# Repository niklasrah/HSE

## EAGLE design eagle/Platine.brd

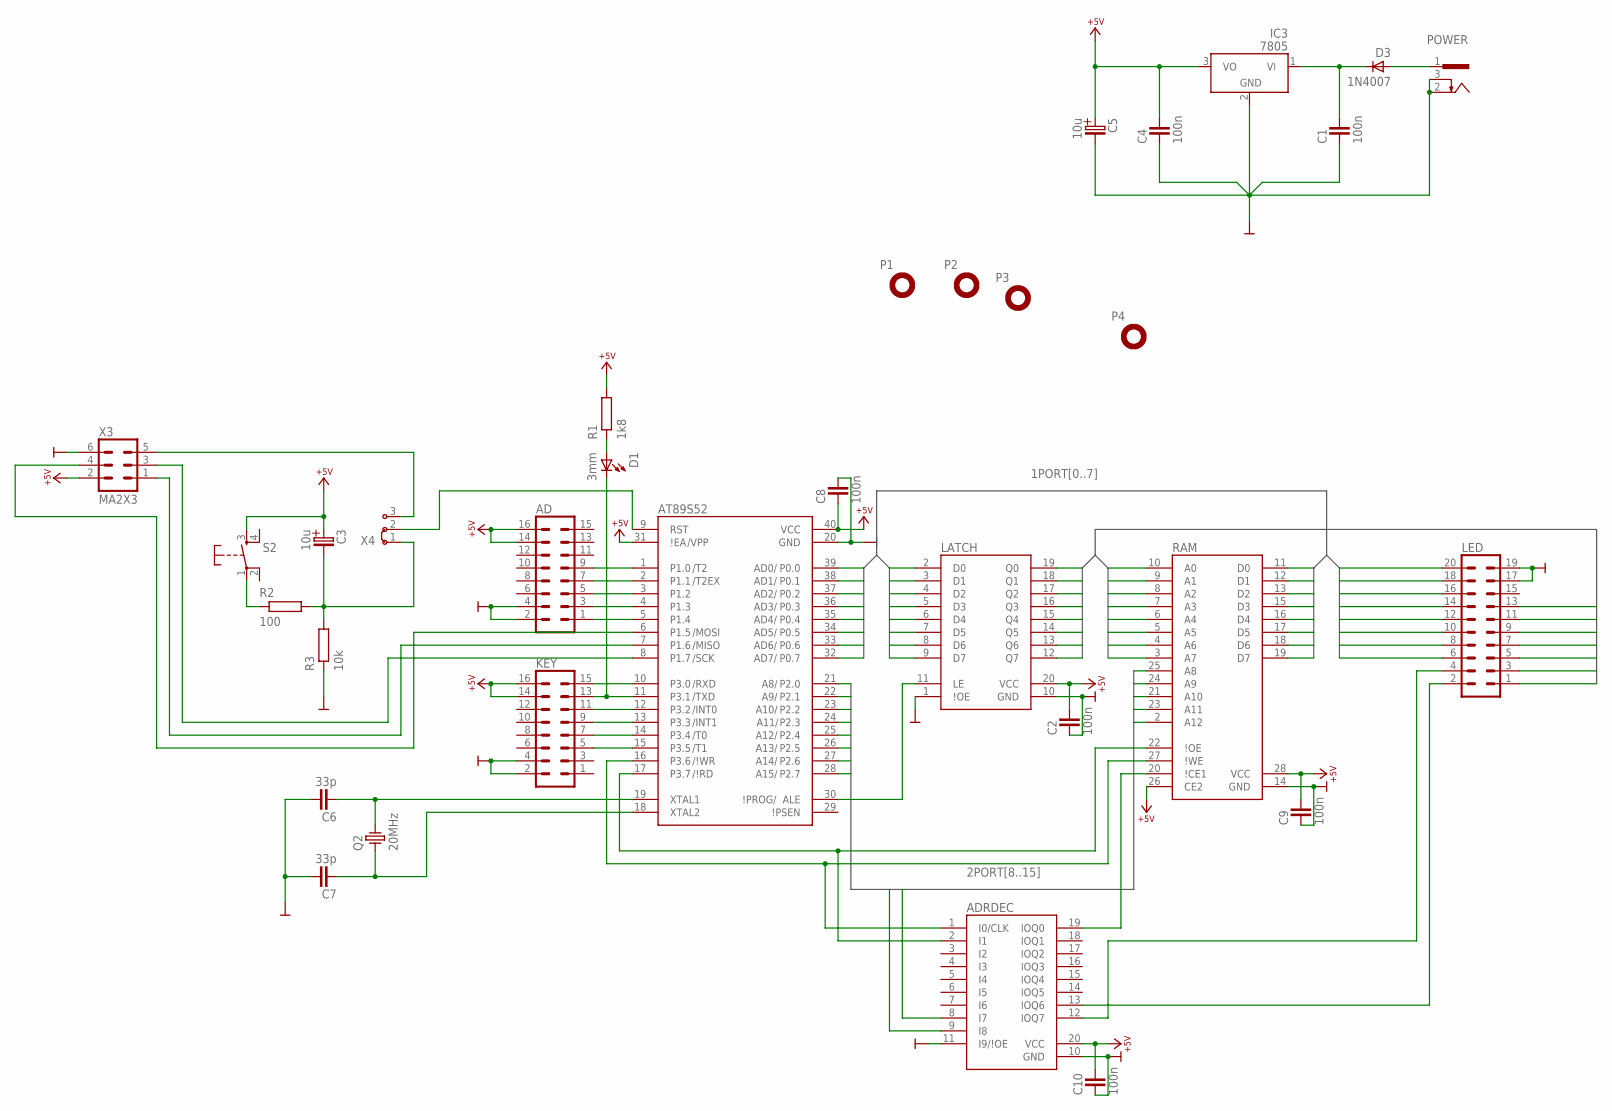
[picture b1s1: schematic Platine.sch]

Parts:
AD: MA8X2
ADRDEC: 16V8; DIL20
AT89S52: AT89S52; DIL40
C1, C2, C4, C8, C9, C10: 100n; C-2,5
C3, C5: 10u; ELKO-2,5
C6, C7: 33p; C-2,5
D1: 3mm; LED3-2,5
D3: 1N4007; DO41-10
IC3: 7805; TO220V
KEY: MA8X2
LATCH: 74573; DIL20
LED: MA10X2
P1, P2, P3, P4: MPAD-3,0
POWER: PWRCON-HEBW21; HEBW21
Q2: 20MHz; HC49U
R1: 1k8; R-10
R2: 100; R-10
R3: 10k; R-10
RAM: 6264; DIL28
S2: KEY-3301; T3301
X3: MA2X3; MA3X2
X4: J1X3

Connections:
1PORT0: AT89S52.39 (P0.0), LATCH.2 (D0), LED.20, RAM.11 (D0)
1PORT1: AT89S52.38 (P0.1), LATCH.3 (D1), LED.18, RAM.12 (D1)
1PORT2: AT89S52.37 (P0.2), LATCH.4 (D2), LED.16, RAM.13 (D2)
1PORT3: AT89S52.36 (P0.3), LATCH.5 (D3), LED.14, RAM.15 (D3)
1PORT4: AT89S52.35 (P0.4), LATCH.6 (D4), LED.12, RAM.16 (D4)
1PORT5: AT89S52.34 (P0.5), LATCH.7 (D5), LED.10, RAM.17 (D5)
1PORT6: AT89S52.33 (P0.6), LATCH.8 (D6), LED.8, RAM.18 (D6)
1PORT7: AT89S52.32 (P0.7), LATCH.9 (D7), LED.6, RAM.19 (D7)
2PORT8: ADRDEC.9 (I8), AT89S52.21 (P2.0), RAM.25 (A8)
2PORT9: ADRDEC.8 (I7), AT89S52.22 (P2.1), RAM.24 (A9)
2PORT10: AT89S52.23 (P2.2), RAM.21 (A10)
2PORT11: AT89S52.24 (P2.3), RAM.23 (A11)
2PORT12: AT89S52.25 (P2.4), RAM.2 (A12)
2PORT13: AT89S52.26 (P2.5)
2PORT14: AT89S52.27 (P2.6)
2PORT15: AT89S52.28 (P2.7)
+5V: AD.14, AD.16, ADRDEC.20 (VCC), AT89S52.31 (\!EA), AT89S52.40 (VCC), C2.2, C3.+, C4.2, C5.+, C8.1, C9.2, C10.2, IC3.3 (VO), KEY.14, KEY.16, LATCH.20 (VCC), R1.2, RAM.26 (CE2), RAM.28 (VCC), S2.3 (S), X3.2
A0: LATCH.19 (Q0), LED.13, RAM.10 (A0)
A1: LATCH.18 (Q1), LED.11, RAM.9 (A1)
A2: LATCH.17 (Q2), LED.9, RAM.8 (A2)
A3: LATCH.16 (Q3), LED.7, RAM.7 (A3)
A4: LATCH.15 (Q4), LED.5, RAM.6 (A4)
A5: LATCH.14 (Q5), LED.3, RAM.5 (A5)
A6: LATCH.13 (Q6), LED.1, RAM.4 (A6)
A7: LATCH.12 (Q7), RAM.3 (A7)
GND: AD.2, AD.4, ADRDEC.10 (GND), ADRDEC.11 (I9/\!OE), AT89S52.20 (GND), C1.1, C2.1, C4.1, C5.-, C6.2, C7.2, C8.2, C9.1, C10.1, IC3.2 (GND), KEY.2, KEY.4, LATCH.1 (\!OE), LATCH.10 (GND), LED.17, LED.19, POWER.2, POWER.3, R3.1, RAM.14 (GND), X3.6
unnamed: AT89S52.9 (RST), X4.2
unnamed: R2.1, S2.1
unnamed: C3.-, R2.2, R3.2, X4.1
unnamed: X3.5, X4.3
unnamed: D3.A, POWER.1
unnamed: C1.2, D3.C, IC3.1 (VI)
unnamed: AT89S52.19 (XTAL1), C6.1, Q2.2
unnamed: AT89S52.10 (P3.0), KEY.15
unnamed: AT89S52.18 (XTAL2), C7.1, Q2.1
unnamed: AT89S52.8 (P1.7), X3.3
unnamed: AT89S52.7 (P1.6), X3.1
unnamed: AT89S52.6 (P1.5), X3.4
unnamed: AT89S52.11 (P3.1), D1.C, KEY.13
unnamed: AT89S52.12 (P3.2), KEY.11
unnamed: AT89S52.13 (P3.3), KEY.9
unnamed: AT89S52.14 (P3.4), KEY.7
unnamed: AT89S52.15 (P3.5), KEY.5
unnamed: AD.1, AT89S52.5 (P1.4)
unnamed: AD.3, AT89S52.4 (P1.3)
unnamed: AD.5, AT89S52.3 (P1.2)
unnamed: AD.7, AT89S52.2 (P1.1)
unnamed: AD.9, AT89S52.1 (P1.0)
unnamed: D1.A, R1.1
unnamed: ADRDEC.2 (I1), AT89S52.17 (P3.7), RAM.22 (\!OE)
unnamed: ADRDEC.1 (I0/CLK), AT89S52.16 (P3.6), RAM.27 (\!WE)
unnamed: ADRDEC.19 (IOQ0), RAM.20 (\!CE1)
unnamed: ADRDEC.12 (IOQ7), LED.4
unnamed: ADRDEC.13 (IOQ6), LED.2
unnamed: AT89S52.30 (ALE), LATCH.11 (LE)

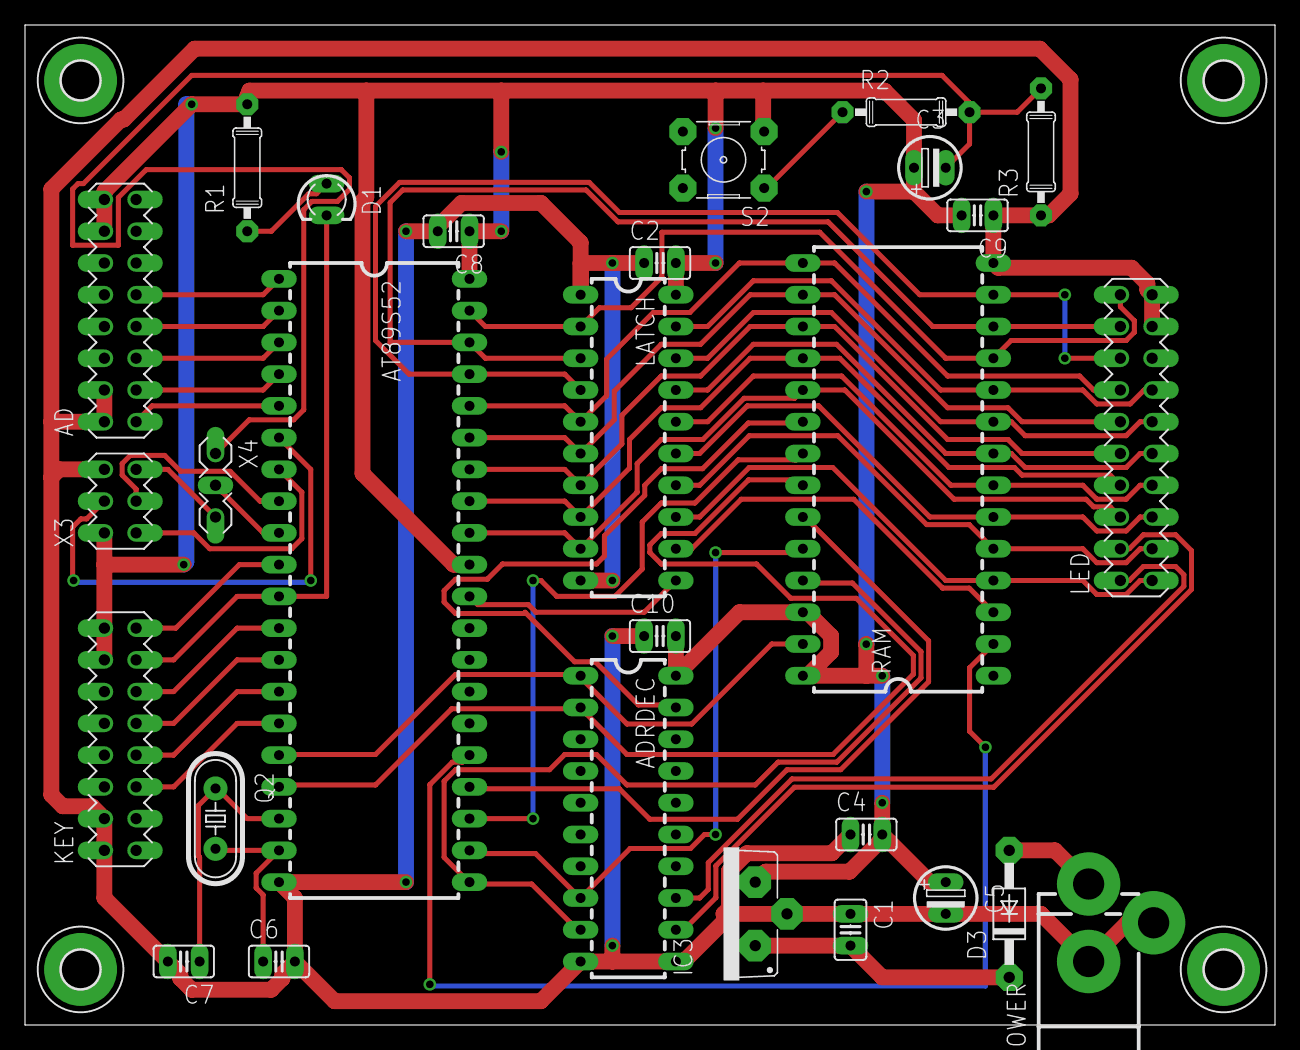
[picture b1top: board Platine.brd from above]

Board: 2 copper layers, 100.0 x 80.0 mm, 32 parts (0 on the bottom side), 52 nets.

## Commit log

2022-11-08 eagle files added
2022-11-17 14 bridges
2022-11-19 4 remaining
2022-11-19 12 bridges total
2022-11-19 quick fix
